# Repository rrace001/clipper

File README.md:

# clipper
Minimalist Musical Instrument Clip on Tuner

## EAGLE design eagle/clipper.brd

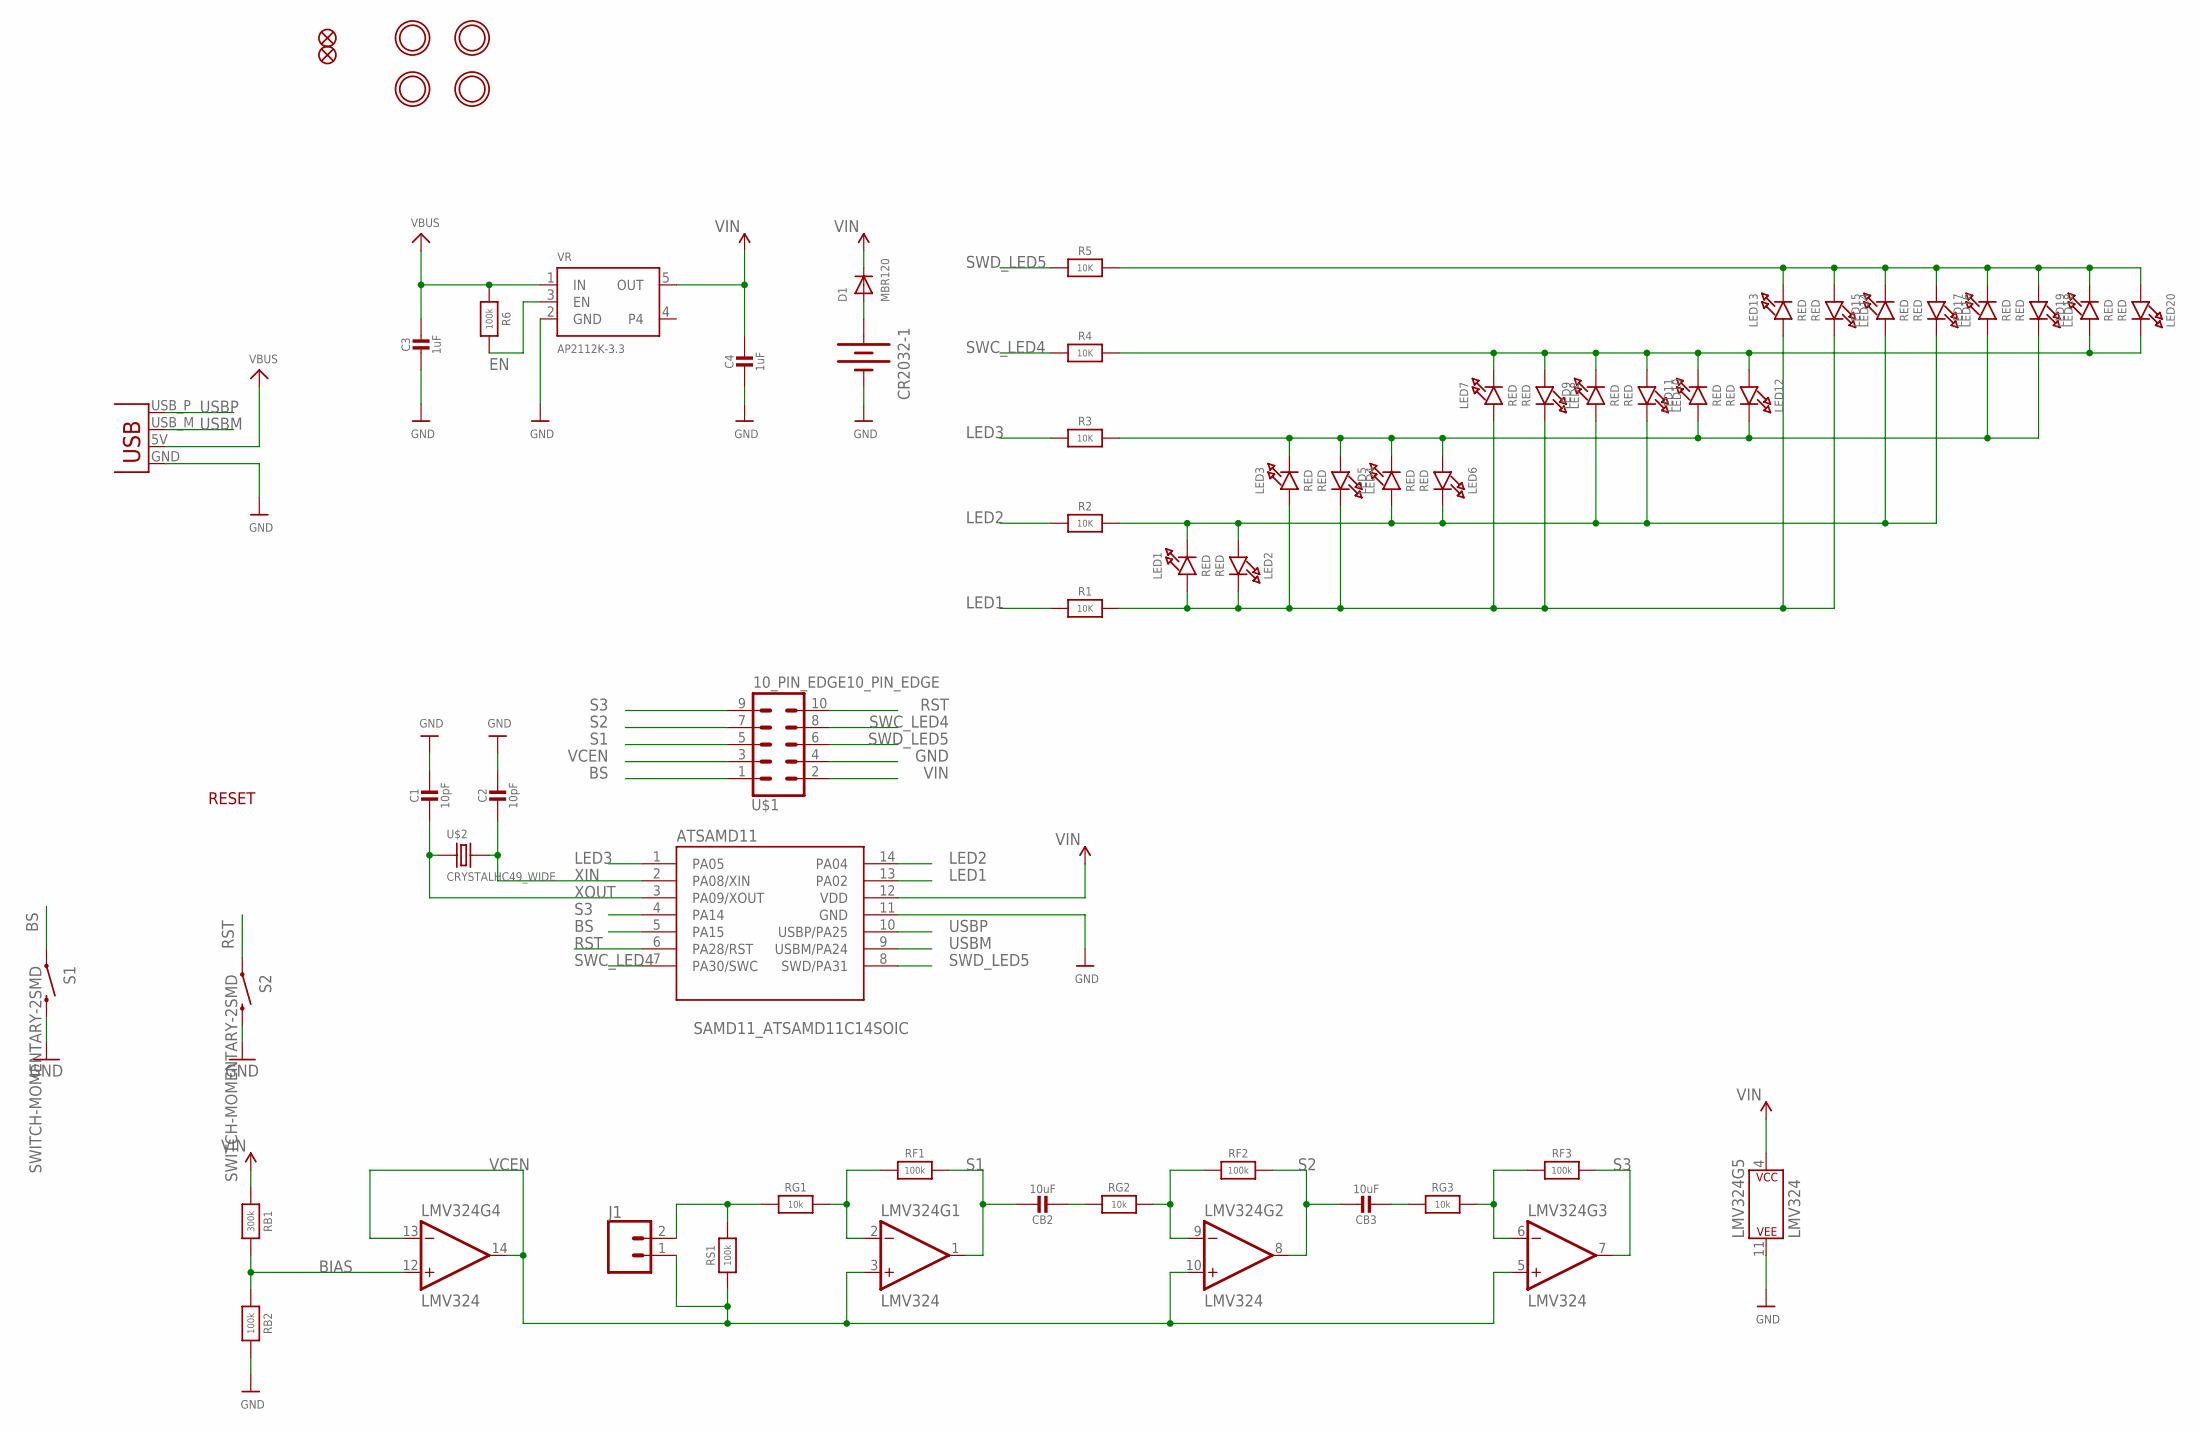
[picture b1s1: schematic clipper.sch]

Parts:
ATSAMD11: SAMD11_ATSAMD11C14SOIC; RRACE001_SO14
C1, C2: 10pF; 0603-NO
C3, C4: 1uF; 0603-NO
CB2, CB3: 10uF; 0603-NO
CR2032-1: BATTERY_20MM_PTH; BATTCOM_20MM_PTH
D1: MBR120; SOD-123FL
J1: CONN_02; 1X02
LED1, LED2, LED3, LED4, LED5, LED6, LED7, LED8, LED9, LED10, LED11, LED12, LED13, LED14, LED15, LED16, LED17, LED18, LED19, LED20: RED; CHIPLED_0603_NOOUTLINE
LMV324: LMV324; SO14
MH1, MH2, MH3, MH4: MOUNTINGHOLE2.5; MOUNTINGHOLE_2.5_PLATED
R1, R2, R3, R4, R5: 10K; 0603-NO
R6: 100k; 0603-NO
RB1: 300k; 0603-NO
RB2: 100k; 0603-NO
RF1, RF2, RF3: 100k; 0603-NO
RG1, RG2, RG3: 10k; 0603-NO
RS1: 100k; 0603-NO
S1, S2: SWITCH-MOMENTARY-2SMD; TACTILE-SWITCH-SMD
U$1: 10_PIN_EDGE10_PIN_EDGE; 10_PIN_EDGE
U$2: CRYSTALHC49_WIDE; HC49U_ALL
U$34, U$35: FIDUCIAL_1MM
VR: AP2112K-3.3; SOT23-5
X4: USBPCB; USB-A-PCB

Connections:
BIAS: LMV324.12 (+IN), RB1.2, RB2.1
BS: ATSAMD11.5 (PA15), S1.1, U$1.1
EN: R6.2, VR.3 (EN)
F1: LMV324.2 (-IN), RF1.1, RG1.2
F2: LMV324.9 (-IN), RF2.1, RG2.2
F3: LMV324.6 (-IN), RF3.1, RG3.2
GND: ATSAMD11.11 (GND), C1.2, C2.2, C3.2, C4.2, CR2032-1.NEG (-), LMV324.11 (P$V-), RB2.2, S1.3 (2), S2.3 (2), U$1.4, VR.2 (GND), X4.GND
IN1: J1.2, RG1.1, RS1.2
IN2: CB2.2, RG2.1
IN3: CB3.2, RG3.1
LED1: ATSAMD11.13 (PA02), R1.1
LED2: ATSAMD11.14 (PA04), R2.1
LED3: ATSAMD11.1 (PA05), R3.1
unnamed: LED1.A, LED2.C, LED3.A, LED4.C, LED7.A, LED8.C, LED13.A, LED14.C, R1.2
unnamed: LED1.C, LED2.A, LED5.A, LED6.C, LED9.A, LED10.C, LED15.A, LED16.C, R2.2
unnamed: LED3.C, LED4.A, LED5.C, LED6.A, LED11.A, LED12.C, LED17.A, LED18.C, R3.2
unnamed: LED13.C, LED14.A, LED15.C, LED16.A, LED17.C, LED18.A, LED19.C, LED20.A, R5.2
unnamed: LED7.C, LED8.A, LED9.C, LED10.A, LED11.C, LED12.A, LED19.A, LED20.C, R4.2
unnamed: CR2032-1.POS (+), D1.A
RST: ATSAMD11.6 (PA28/RST), S2.1, U$1.10
S1: CB2.1, LMV324.1 (OUT), RF1.2, U$1.5
S2: CB3.1, LMV324.8 (OUT), RF2.2, U$1.7
S3: ATSAMD11.4 (PA14), LMV324.7 (OUT), RF3.2, U$1.9
SWC_LED4: ATSAMD11.7 (PA30/SWC), R4.1, U$1.8
SWD_LED5: ATSAMD11.8 (SWD/PA31), R5.1, U$1.6
USBM: ATSAMD11.9 (USBM/PA24), X4.USB_M (D-)
USBP: ATSAMD11.10 (USBP/PA25), X4.USB_P (D+)
VBUS: C3.1, R6.1, VR.1 (IN), X4.5V (VBUS)
VCEN: J1.1, LMV324.3 (+IN), LMV324.5 (+IN), LMV324.10 (+IN), LMV324.13 (-IN), LMV324.14 (OUT), RS1.1, U$1.3
VIN: ATSAMD11.12 (VDD), C4.1, D1.C, LMV324.4 (P$V+), RB1.1, U$1.2, VR.5 (OUT)
XIN: ATSAMD11.2 (PA08/XIN), C2.1, U$2.2
XOUT: ATSAMD11.3 (PA09/XOUT), C1.1, U$2.1

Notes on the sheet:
RESET

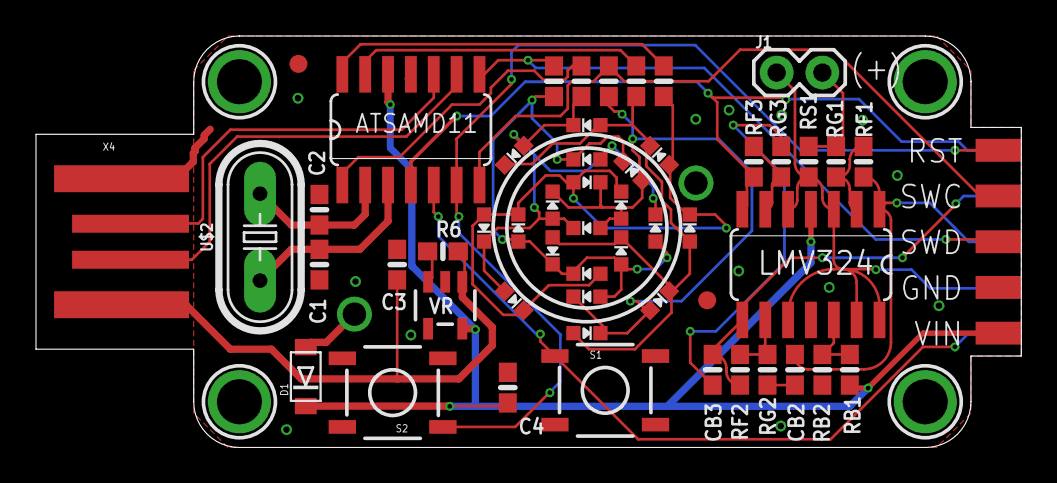
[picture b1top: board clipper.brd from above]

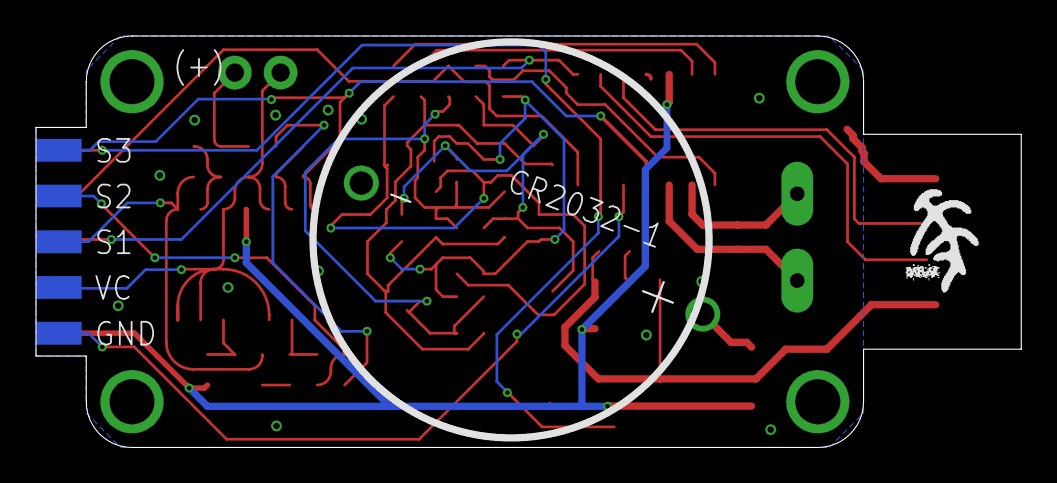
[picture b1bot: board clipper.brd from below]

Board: 2 copper layers, 54.7 x 22.9 mm, 58 parts (2 on the bottom side), 32 nets.

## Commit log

2019-08-20 Create temp
2019-08-20 added eagle files
2019-08-20 gitignore
2019-08-20 cleaining
2019-08-20 cleaning
2019-08-23 added strobe test

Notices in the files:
parts and their libraries:
microbuilder: This work is placed in the public domain, and may be freely used for commercial and non-commercial work with the following conditions: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
SparkFun-Connectors: Licensing: Creative Commons ShareAlike 4.0 International - https://creativecommons.org/licenses/by-sa/4.0
